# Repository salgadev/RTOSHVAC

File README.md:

**Writen in C POSIX.**

*Software used:*
- MPLAB IDE
- RT-PReempt Linux Kernel
- PICC C Compiler
- Minicom (Linux)
- HyperTerminal (Windows debugging)

*Hardware used:* 

- PIC16F887 PIC microcontroller
- MAX232A TTL IC
- 2N6507 Sillicon-Controlled Rectifier
- MOC3011 TRIAC
- LM35 Thermistor
- PICKit 2
- Polarization circuits in protoboard
- PCB for power circuit
- Null-modem RS232 cable

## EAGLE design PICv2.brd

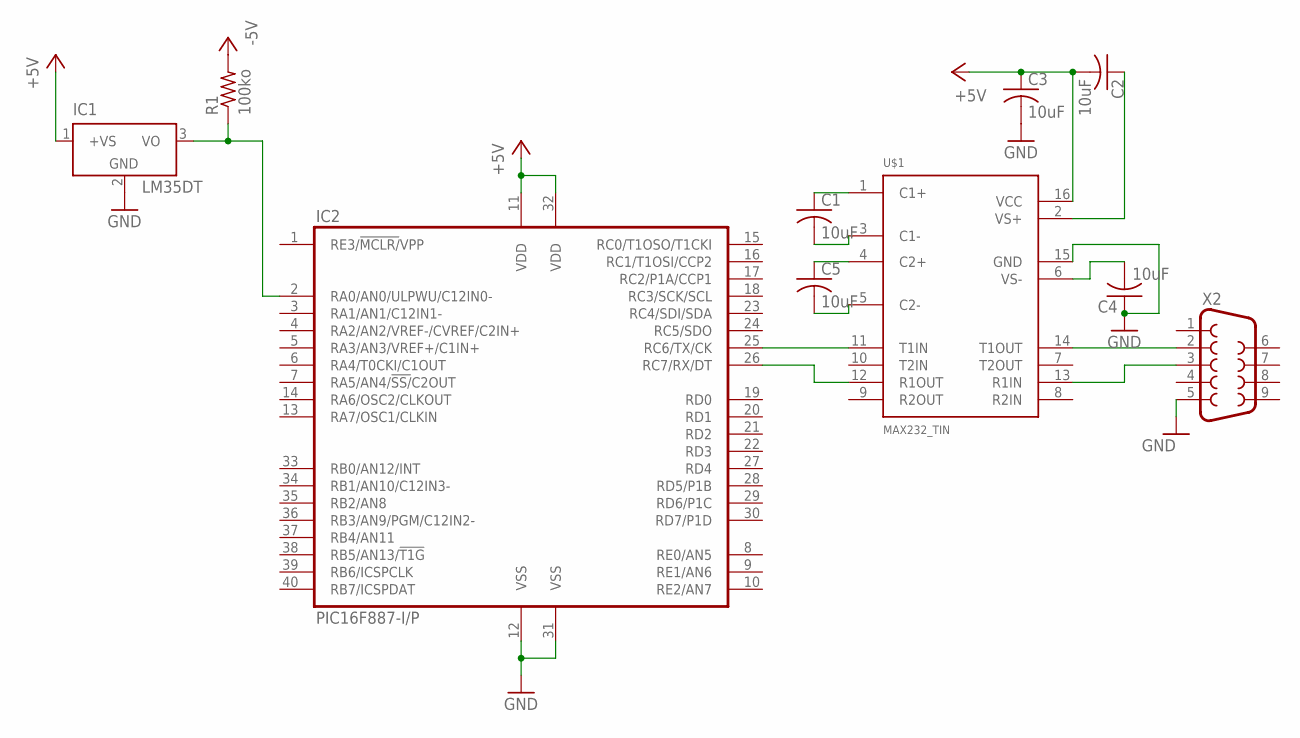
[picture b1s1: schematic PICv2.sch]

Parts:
C1, C2, C3, C4, C5: 10uF; C0805; MPN CGA2B1X7R1C104K050BC
IC1: LM35DT; TO220V; MPN LM35AH
IC2: PIC16F887-I/P; DIL40; MPN PIC16F887-I/P
R1: 100ko; M0805; MPN ERJ-1GNF1003C
U$1: MAX232_TIN; DIL16; MPN MAX232EIDR
X2: F09D

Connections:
+5V: C2.2, C3.1, IC1.1 (+VS), IC2.11 (VDD), IC2.32 (VDD), U$1.16 (VCC)
-5V: R1.2
GND: C3.2, C4.1, IC1.2 (GND), IC2.12 (VSS), IC2.31 (VSS), U$1.15 (GND), X2.5
unnamed: C1.1, U$1.1 (C1+)
unnamed: C1.2, U$1.3 (C1-)
unnamed: C5.1, U$1.4 (C2+)
unnamed: C5.2, U$1.5 (C2-)
unnamed: IC1.3 (VO), IC2.2 (RA0/AN0/ULPWU/C12IN0-), R1.1
unnamed: C2.1, U$1.2 (VS+)
unnamed: C4.2, U$1.6 (VS-)
unnamed: IC2.25 (RC6/TX/CK), U$1.11 (T1IN)
unnamed: IC2.26 (RC7/RX/DT), U$1.12 (R1OUT)
unnamed: U$1.14 (T1OUT), X2.2
unnamed: U$1.13 (R1IN), X2.3

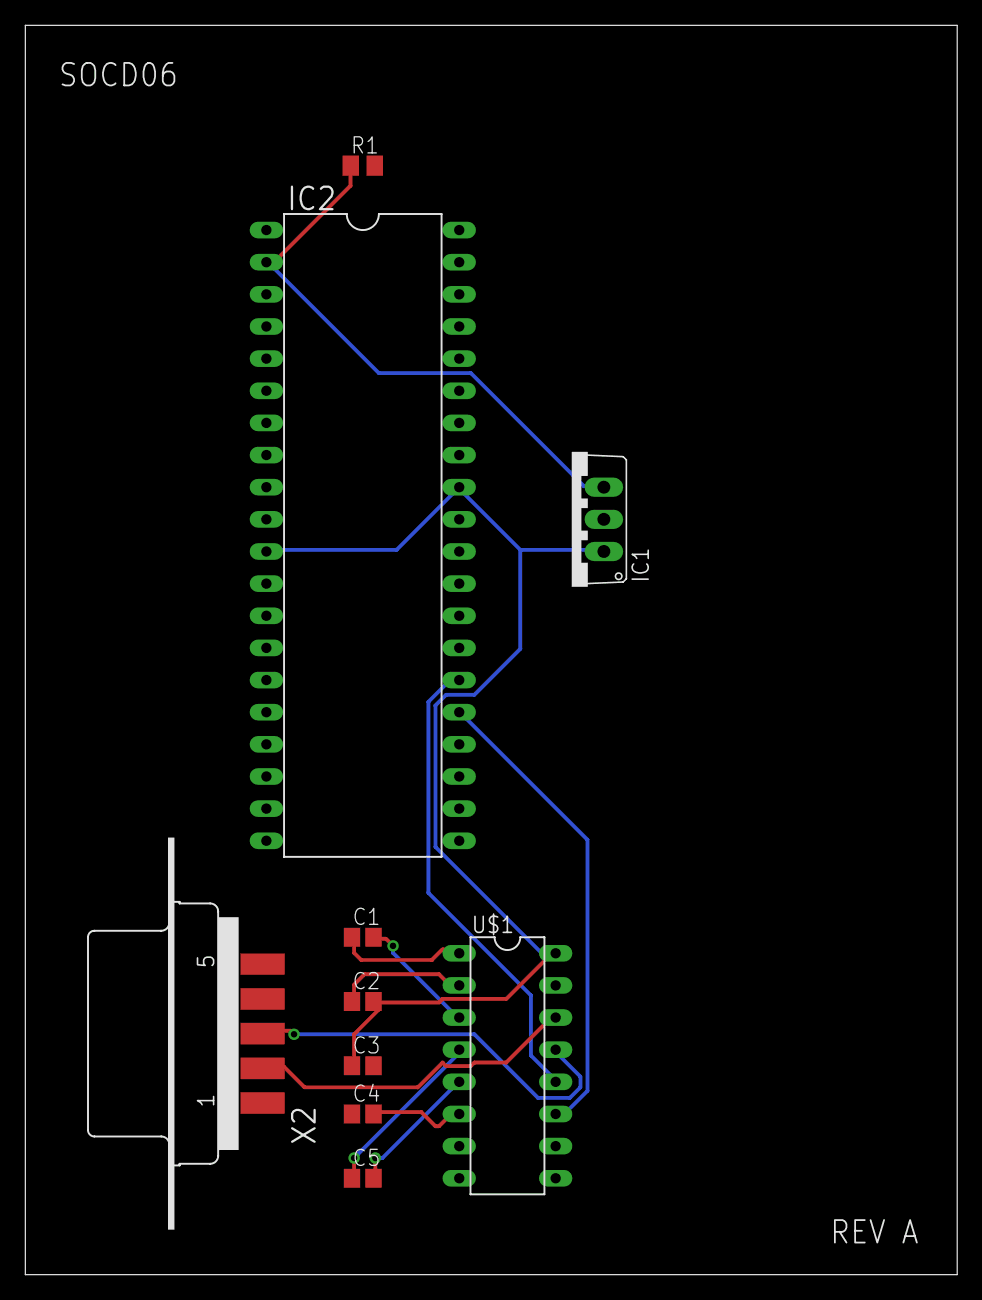
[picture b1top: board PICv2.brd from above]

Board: 2 copper layers, 73.6 x 98.7 mm, 10 parts (0 on the bottom side), 13 nets.

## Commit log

2019-06-15 Final year mechatronics engineering project
2019-06-15 Translated first comment from Spanish
2019-06-15 Updated variable names and comments.
2019-08-03 Added pictures
2019-08-03 Added PIC board and schematic files
